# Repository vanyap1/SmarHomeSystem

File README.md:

# SmarHomeSystem
My smart home controllers

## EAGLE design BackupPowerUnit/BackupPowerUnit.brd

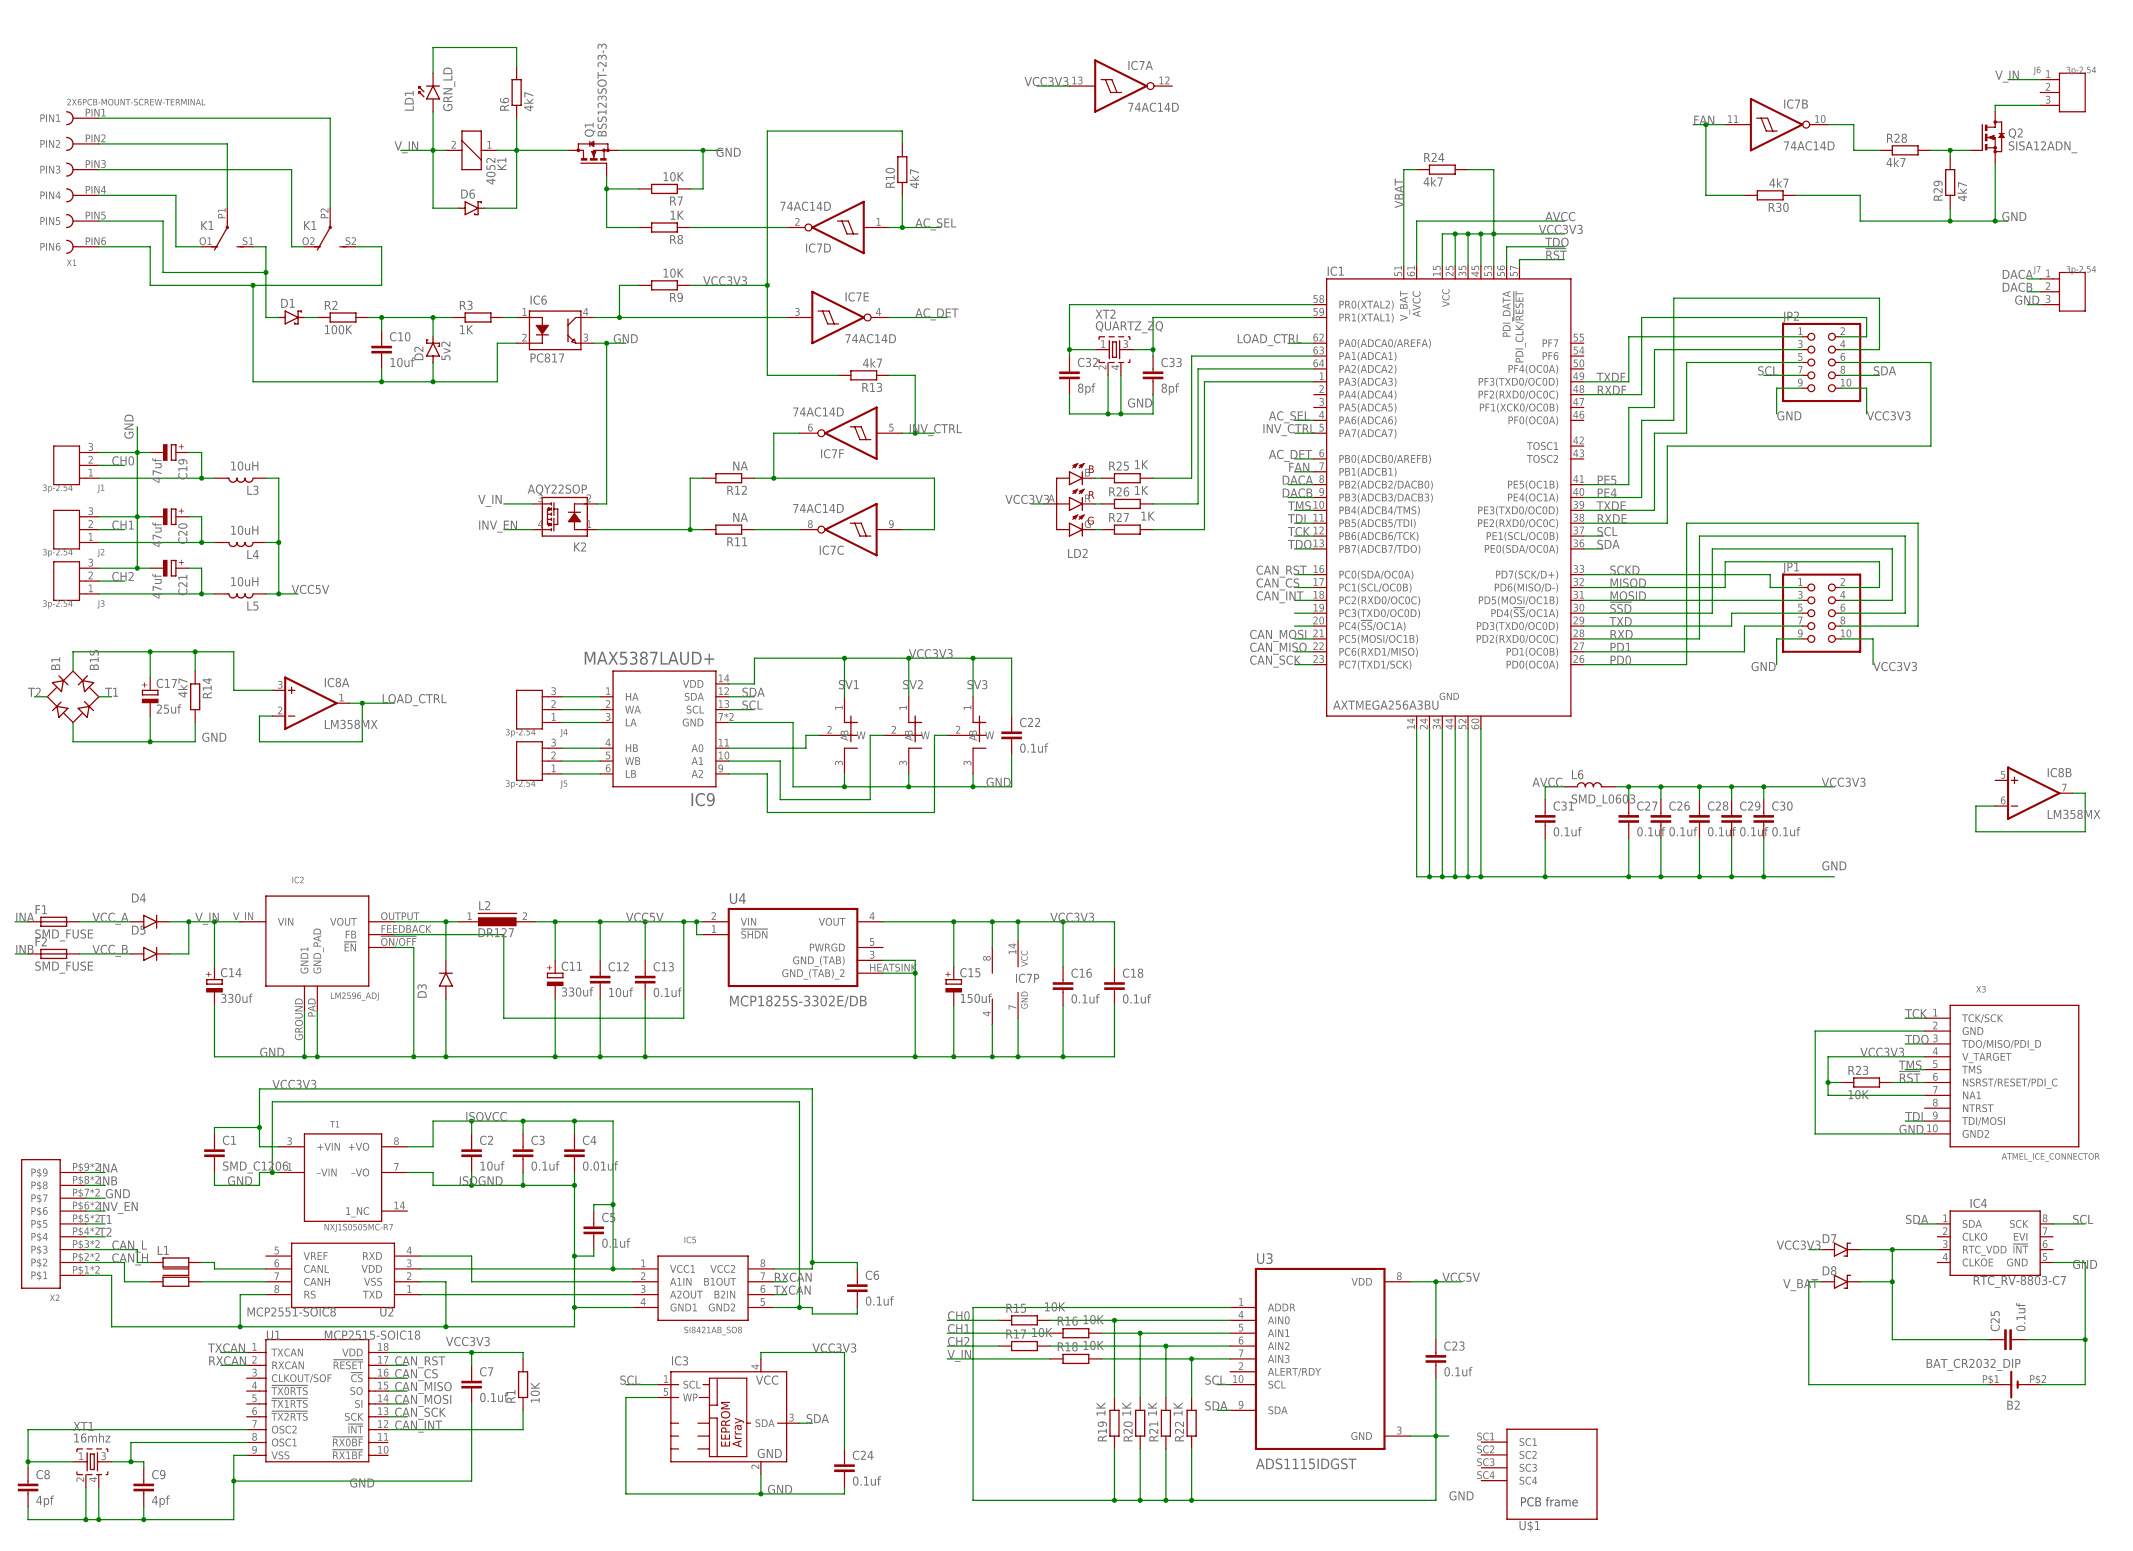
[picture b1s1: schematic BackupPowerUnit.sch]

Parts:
B1: B1S; MBS
B2: BAT_CR2032_DIP; CR2032_DIP
C1: SMD_C1206; 1206
C2, C12: 10uf; 1206
C3, C5, C6, C7, C13, C16, C18, C22, C23, C24, C25, C26, C27, C28, C29, C30, C31: 0.1uf; 0603
C4: 0.01uf; 0603
C8, C9: 4pf; 0603
C10: 10uf; 0805
C11, C14: 330uf; 3.6MM
C15: 150uf; KA-3528ASYC
C17: 25uf; KA-3528ASYC
C19, C20, C21: 47uf; KA-3528ASYC
C32, C33: 8pf; 0603
D1, D6: 1N5819-B; DO41-7.6
D2: 5v2; DO41-7.6
D3, D4, D5: D_MBRA340G; SMA403D
D7, D8: D_SOD323; SOD-323_D
F1, F2: SMD_FUSE; SMD_2410_FUSE_NOK
IC1: AXTMEGA256A3BU; TQFP64
IC2: LM2596_ADJ; DDPAK/TO-263(S)
IC3: MICROCHIP-24AA01T-I/OT; SOT-23(5)
IC4: RTC_RV-8803-C7; C7_RTC
IC5: SI8421AB_SO8; SO8
IC6: PC817; DIL4-SMD
IC7: 74AC14D; SO14
IC8: LM358MX; SO08
IC9: MAX5387LAUD+; SOP65P640X110-14N
J1, J2, J3, J4, J5, J6, J7: 3p-2.54; H3-2.54-7.62X5.8MM
JP1, JP2: PINHD-2X5; 2X05
K1: 4052; F4052
K2: AQY22SOP; SOP04
L1: EPCOS_B82793_FILTER; EPCOS_FILTER
L2: DR127
L3, L4, L5: 10uH; 0603
L6: SMD_L0603; 0603
LD1: GRN_LD; 0603_P
LD2: LTSN-N213EGBW(RGB_LED); LTSN-N213EGBW
Q1: BSS123SOT-23-3; SOT-23(3)
Q2: SISA12ADN_; VISHAY_SIS468DN-T1-GE3
R1, R7, R9, R15, R16, R17, R18, R23: 10K; 0603
R2: 100K; 0204/7
R3, R8, R19, R20, R21, R22, R25, R26, R27: 1K; 0603
R6, R10, R13, R14, R24, R28, R29, R30: 4k7; 0603
R11, R12: NA; 0603
SV1, SV2, SV3: SMD_SWITCH_JUMPER; 0603_JUMP
T1: NXJ1S0505MC-R7; NXJ1SXXXXMC
U1: MCP2515-SOIC18; SO18L
U2: MCP2551-SOIC8; SO8
U3: ADS1115IDGST; SOP50P490X110-10N
U4: MCP1825S-3302E/DB; SOT230P700X180-4N
U$1: JLC_PCB_FRAME80X100_FRAME; 80X100_PCB_FRAME
X1: 2X6PCB-MOUNT-SCREW-TERMINAL
X2: WAGO250_X9; WAGO250_FP_9X
X3: ATMEL_ICE_CONNECTOR; MINI10P_SPI/JTAG/PDI
XT1: 16mhz; QUARTZ_3X3MM
XT2: QUARTZ_ZQ; QUARTZ_3X3MM

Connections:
!RST: IC1.57 (PDI_CLK/!RESET!), R23.2, X3.6 (NSRST/RESET/PDI_C)
!SSD: IC1.30 (PD4(!SS!/OC1A)), JP1.4
AC_DET: IC1.6 (PB0(ADCB0/AREFB)), IC7.4 (O)
AC_SEL: IC1.4 (PA6(ADCA6)), IC7.1 (I), R10.1
AVCC: C31.1, IC1.61 (AVCC), L6.1
CAN_CS: IC1.17 (PC1(SCL/OC0B)), U1.16 (!CS)
CAN_H: L1.P$2 (2), X2.P$2, X2.U$2
CAN_INT: IC1.18 (PC2(RXD0/OC0C)), R1.1, U1.12 (!INT)
CAN_L: L1.P$1 (1), X2.P$3, X2.U$3
CAN_MISO: IC1.22 (PC6(RXD1/MISO)), U1.15 (SO)
CAN_MOSI: IC1.21 (PC5(MOSI/OC1B)), U1.14 (SI)
CAN_RST: IC1.16 (PC0(SDA/OC0A)), U1.17 (!RESET)
CAN_SCK: IC1.23 (PC7(TXD1/SCK)), U1.13 (SCK)
CH0: J1.2, R15.1
CH1: J2.2, R16.1
CH2: J3.2, R17.1
DACA: IC1.8 (PB2(ADCB2/DACB0)), J7.1
DACB: IC1.9 (PB3(ADCB3/DACB3)), J7.2
FAN: IC1.7 (PB1(ADCB1)), IC7.11 (I), R30.2
GND: B1.-, B2.P$2 (-), C1.2, C6.2, C7.2, C8.2, C9.2, C11.P$1 (-), C12.2, C13.2, C14.P$1 (-), C15.M (-), C16.2, C17.M (-), C18.2, C19.M (-), C20.M (-), C21.M (-), C22.2, C23.2, C24.2, C25.2, C26.2, C27.2, C28.2, C29.2, C30.2, C31.2, C32.2, C33.2, D3.P$2 (A), IC1.14 (GND1), IC1.24 (GND2), IC1.34 (GND3), IC1.44 (GND4), IC1.52 (GND5), IC1.60 (GND6), IC2.!ON/OFF (!EN!), IC2.GROUND (GND1), IC2.PAD (GND_PAD), IC3.2 (GND), IC3.5 (WP), IC4.5 (GND), IC5.5 (GND2), IC6.3 (E), IC7.7 (GND), IC8.4 (V-), IC9.7 (GND), IC9.8 (GND), J1.3, J2.3, J3.3, J7.3, JP1.9, JP2.9, K2.2 (K), Q1.2 (S), Q2.1 (S), Q2.2 (S), Q2.3 (S), R7.1, R14.2, R19.1, R20.1, R21.1, R22.1, R29.1, R30.1, SV1.3 (B), SV2.3 (B), SV3.3 (B), T1.1 (–VIN), U1.9 (VSS), U3.1 (ADDR), U3.3 (GND), U4.3 (GND_(TAB)), U4.HEATSINK (GND_(TAB)_2), X2.P$7, X2.U$7, X3.2 (GND), X3.10 (GND2), XT1.2, XT1.4, XT2.2, XT2.4
INA: F1.P$1 (1), X2.P$9, X2.U$9
INB: F2.P$1 (1), X2.P$8, X2.U$8
INV_CTRL: IC1.5 (PA7(ADCA7)), IC7.5 (I), R13.1
INV_EN: K2.4 (DS1), X2.P$6, X2.U$6
ISOGND: C2.2, C3.2, C4.2, C5.2, IC5.4 (GND1), T1.7 (–VO), U2.2 (VSS), U2.8 (RS), X2.P$1, X2.U$1
ISOVCC: C2.1, C3.1, C4.1, C5.1, IC5.1 (VCC1), T1.8 (+VO), U2.3 (VDD)
LOAD_CTRL: IC1.62 (PA0(ADCA0/AREFA)), IC8.1 (OUT), IC8.2 (-IN)
MISOD: IC1.32 (PD6(MISO/D-)), JP1.2
MOSID: IC1.31 (PD5(MOSI/OC1B)), JP1.3
unnamed: D1.A, K1.S1 (S), X1.PIN5
unnamed: K1.O1 (O), X1.PIN4
unnamed: K1.O2 (O), X1.PIN3
unnamed: Q1.1 (G), R7.2, R8.2
unnamed: K1.P1, X1.PIN2
unnamed: K1.P2, X1.PIN1
unnamed: L1.P$3 (3), U2.7 (CANH)
unnamed: L1.P$4 (4), U2.6 (CANL)
unnamed: IC7.6 (O), IC7.9 (I), R12.1
unnamed: IC6.4 (C), IC7.3 (I), R9.2
unnamed: IC5.2 (A1IN), U2.4 (RXD)
unnamed: C9.1, U1.8 (OSC1), XT1.3
unnamed: C8.1, U1.7 (OSC2), XT1.1
unnamed: IC5.3 (A2OUT), U2.1 (TXD)
unnamed: IC6.1 (ANODE), R3.2
unnamed: D3.P$1 (C), IC2.OUTPUT (VOUT), L2.1
unnamed: C10.2, D2.A, IC6.2 (KATODE), K1.S2 (S), X1.PIN6
unnamed: D1.C, R2.1
unnamed: C10.1, D2.C, R2.2, R3.1
unnamed: LD1.1 (K), R6.2
unnamed: D6.C, K1.1, Q1.3 (D), R6.1
unnamed: IC7.2 (O), R8.1
unnamed: K2.1 (A), R11.2, R12.2
unnamed: IC7.8 (O), R11.1
unnamed: IC9.11 (A0), SV1.2 (W)
unnamed: IC8.6 (-IN), IC8.7 (OUT)
unnamed: B1.+, C17.P (+), IC8.3 (+IN), R14.1
unnamed: C19.P (+), J1.1, L3.2
unnamed: IC9.10 (A1), SV2.2 (W)
unnamed: C20.P (+), J2.1, L4.2
unnamed: IC9.9 (A2), SV3.2 (W)
unnamed: C21.P (+), J3.1, L5.2
unnamed: C25.1, D7.K, D8.K, IC4.3 (RTC_VDD)
unnamed: IC9.1 (HA), J4.3
unnamed: IC9.2 (WA), J4.2
unnamed: IC7.10 (O), R28.1
unnamed: IC9.3 (LA), J4.1
unnamed: IC9.4 (HB), J5.3
unnamed: IC9.5 (WB), J5.2
unnamed: IC9.6 (LB), J5.1
unnamed: C33.1, IC1.59 (PR1(XTAL1)), XT2.3
unnamed: R15.2, R19.2, U3.4 (AIN0)
unnamed: R16.2, R20.2, U3.5 (AIN1)
unnamed: R17.2, R21.2, U3.6 (AIN2)
unnamed: R18.2, R22.2, U3.7 (AIN3)
unnamed: C32.1, IC1.58 (PR0(XTAL2)), XT2.1
unnamed: LD2.B (BC), R25.1
unnamed: LD2.R (RC), R26.1
unnamed: LD2.G (GC), R27.1
unnamed: IC1.63 (PA1(ADCA1)), R25.2
unnamed: IC1.64 (PA2(ADCA2)), R26.2
unnamed: IC1.1 (PA3(ADCA3)), R27.2
unnamed: J6.3, Q2.5 (D), Q2.6 (D), Q2.7 (D), Q2.8 (D), Q2.9 (D)
unnamed: Q2.4 (G), R28.2, R29.2
PD0: IC1.26 (PD0(OC0A)), JP1.8
PD1: IC1.27 (PD1(OC0B)), JP1.7
PE4: IC1.40 (PE4(OC1A)), JP2.4
PE5: IC1.41 (PE5(OC1B)), JP2.3
RXCAN: IC5.7 (B1OUT), U1.2 (RXCAN)
RXD: IC1.28 (PD2(RXD0/OC0C)), JP1.6
RXDE: IC1.38 (PE2(RXD0/OC0C)), JP2.6
RXDF: IC1.48 (PF2(RXD0/OC0C)), JP2.2
SCKD: IC1.33 (PD7(SCK/D+)), JP1.1
SCL: IC1.37 (PE1(SCL/OC0B)), IC3.1 (SCL), IC4.8 (SCK), IC9.13 (SCL), JP2.7, U3.10 (SCL)
SDA: IC1.36 (PE0(SDA/OC0A)), IC3.3 (SDA), IC4.1 (SDA), IC9.12 (SDA), JP2.8, U3.9 (SDA)
T1: B1.AC2, X2.P$5, X2.U$5
T2: B1.AC1, X2.P$4, X2.U$4
TCK: IC1.12 (PB6(ADCB6/TCK)), X3.1 (TCK/SCK)
TDI: IC1.11 (PB5(ADCB5/TDI)), X3.9 (TDI/MOSI)
TDO: IC1.13 (PB7(ADCB7/TDO)), IC1.56 (PDI_DATA), X3.3 (TDO/MISO/PDI_D)
TMS: IC1.10 (PB4(ADCB4/TMS)), X3.5 (TMS)
TXCAN: IC5.6 (B2IN), U1.1 (TXCAN)
TXD: IC1.29 (PD3(TXD0/OC0D)), JP1.5
TXDE: IC1.39 (PE3(TXD0/OC0D)), JP2.5
TXDF: IC1.49 (PF3(TXD0/OC0D)), JP2.1
VBAT: IC1.51 (V_BAT), R24.1
VCC3V3: C1.1, C6.1, C7.1, C15.P (+), C16.1, C18.1, C22.1, C24.1, C26.1, C27.1, C28.1, C29.1, C30.1, D7.A, IC1.15 (VCC1), IC1.25 (VCC2), IC1.35 (VCC3), IC1.45 (VCC4), IC1.53 (VCC5), IC3.4 (VCC), IC5.8 (VCC2), IC7.13 (I), IC7.14 (VCC), IC8.8 (V+), IC9.14 (VDD), JP1.10, JP2.10, L6.2, LD2.A, R1.2, R9.1, R10.2, R13.2, R23.1, R24.2, SV1.1 (A), SV2.1 (A), SV3.1 (A), T1.3 (+VIN), U1.18 (VDD), U4.4 (VOUT), X3.4 (V_TARGET), X3.7 (NA1)
VCC5V: C11.P$2 (+), C12.1, C13.1, C23.1, IC2.FEEDBACK (FB), L2.2, L3.1, L4.1, L5.1, U3.8 (VDD), U4.1 (!SHDN), U4.2 (VIN)
VCC_A: D4.P$2 (A), F1.P$2 (2)
VCC_B: D5.P$2 (A), F2.P$2 (2)
V_BAT: B2.P$1 (+), D8.A
V_IN: C14.P$2 (+), D4.P$1 (C), D5.P$1 (C), D6.A, IC2.V_IN (VIN), J6.1, K1.2, K2.3 (DS2), LD1.2 (A), R18.1

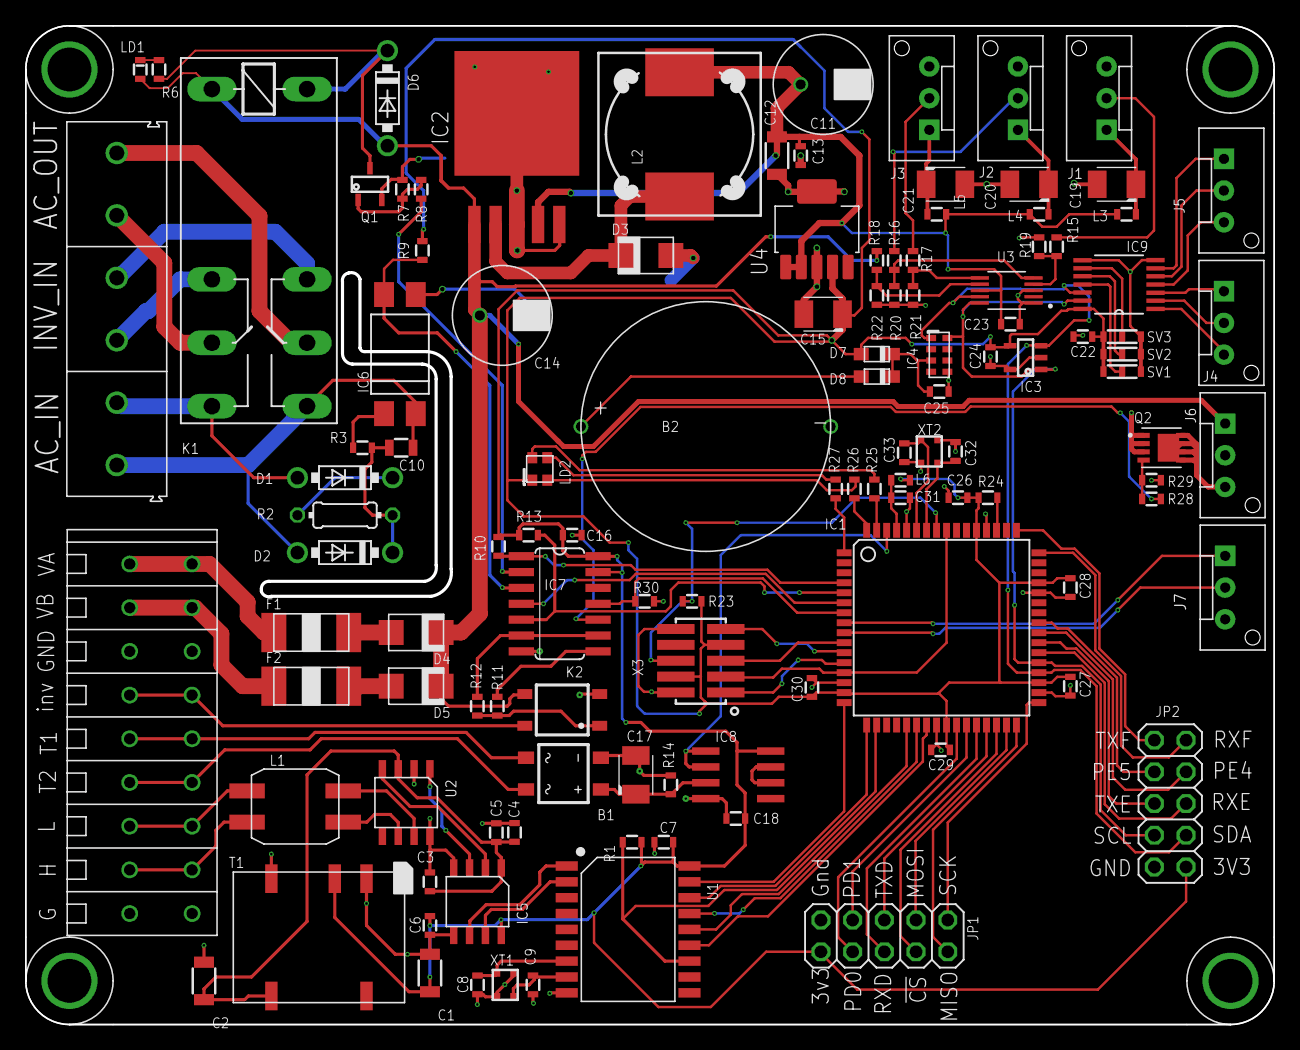
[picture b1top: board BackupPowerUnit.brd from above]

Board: 2 copper layers, 100.0 x 80.0 mm, 117 parts (0 on the bottom side), 111 nets.

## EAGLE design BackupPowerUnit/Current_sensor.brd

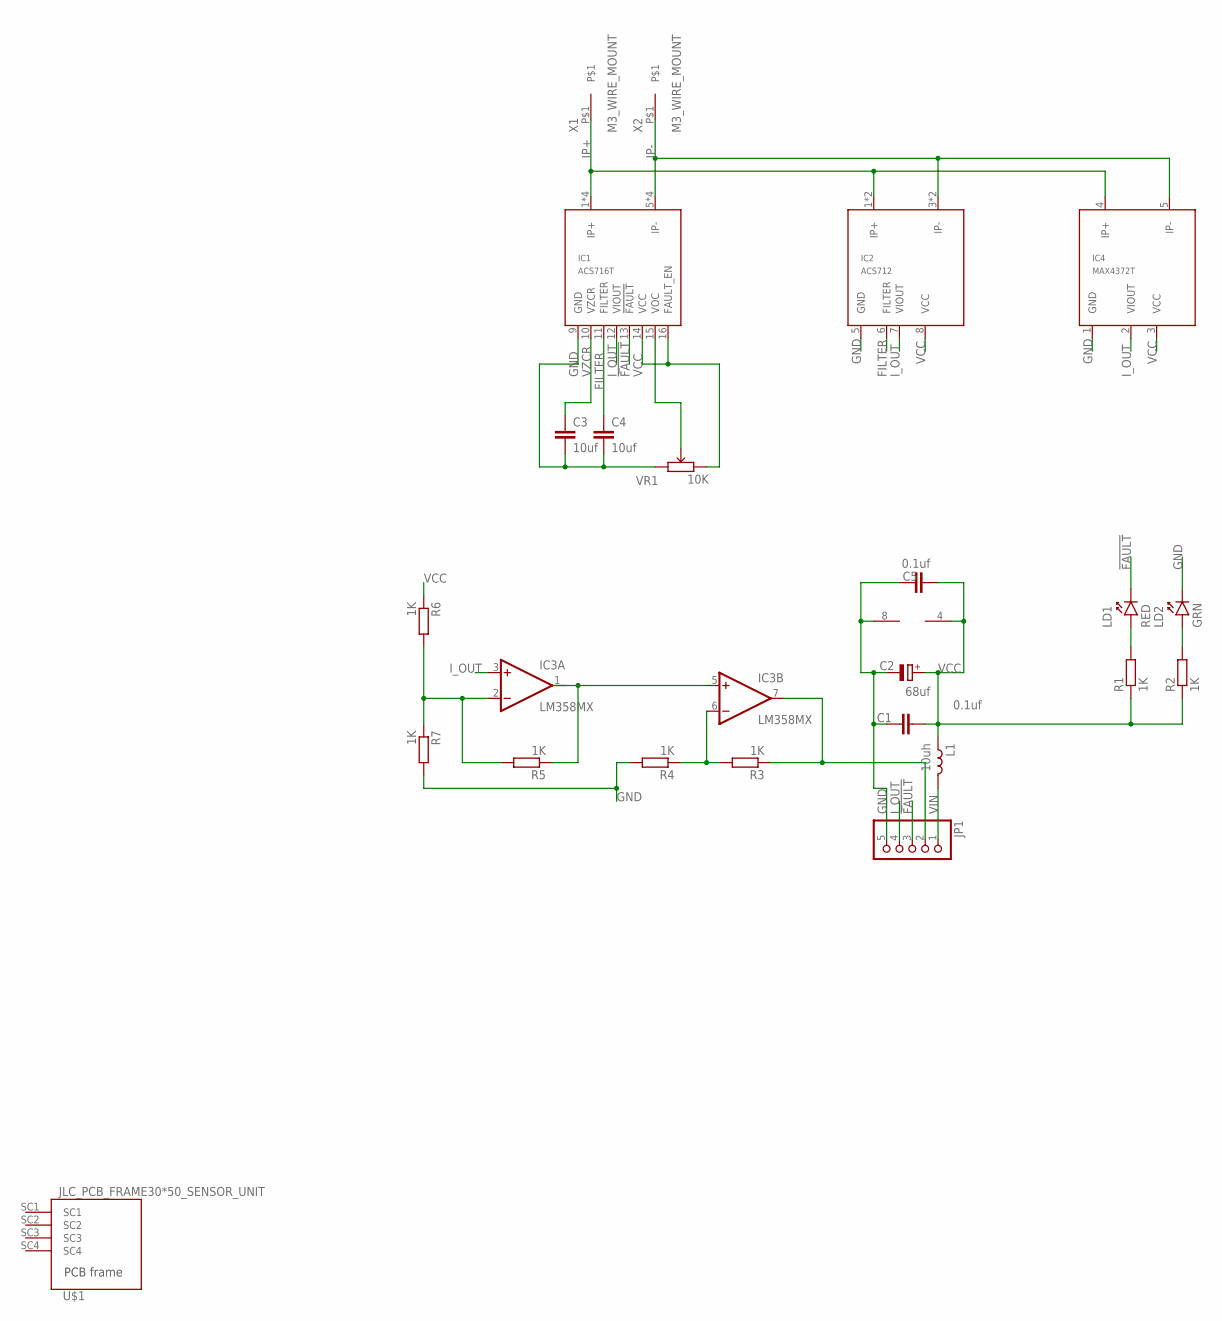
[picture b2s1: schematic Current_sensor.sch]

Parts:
C1, C5: 0.1uf; 0603
C2: 68uf; D/7343-31R
C3, C4: 10uf; 0805
IC1: ACS716T; SO16L
IC2: ACS712; SO8
IC3: LM358MX; SO08
IC4: MAX4372T; SOT-23(5)
JP1: PINHD-1X55X2MM; 1_05X2MM
L1: 10uh; 0603
LD1: RED; 0603_P
LD2: GRN; 0603_P
R1, R2, R3, R4, R5, R6, R7: 1K; 0603
U$1: JLC_PCB_FRAME30*50_SENSOR_UNIT; 30X50_SENSOR_UNIT
VR1: 10K; RESISTOR_VARIABLE
X1, X2: M3_WIRE_MOUNT

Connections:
!FAULT: IC1.13 (!FAULT), JP1.3, LD1.1 (K)
FILTER: C4.1, IC1.11 (FILTER), IC2.6 (FILTER)
GND: C1.1, C2.-, C3.2, C4.2, C5.1, IC1.9 (GND), IC2.5 (GND), IC3.8 (V+), IC4.1 (GND), JP1.5, LD2.1 (K), R4.2, R7.2, VR1.L
IP+: IC1.1 (IP+), IC1.2 (IP+), IC1.3 (IP+), IC1.4 (IP+), IC2.1 (IP+), IC2.2 (IP+), IC4.4 (IP+), X1.P$1
IP-: IC1.5 (IP-), IC1.6 (IP-), IC1.7 (IP-), IC1.8 (IP-), IC2.3 (IP-), IC2.4 (IP-), IC4.5 (IP-), X2.P$1
I_OUT: IC1.12 (VIOUT), IC2.7 (VIOUT), IC3.3 (+IN), IC4.2 (VIOUT), JP1.4
unnamed: IC3.1 (OUT), IC3.5 (+IN), R5.1
unnamed: IC3.6 (-IN), R3.2, R4.1
unnamed: IC3.7 (OUT), JP1.2, R3.1
unnamed: LD1.2 (A), R1.2
unnamed: LD2.2 (A), R2.2
unnamed: IC1.15 (VOC), VR1.W
unnamed: IC3.2 (-IN), R5.2, R6.2, R7.1
VCC: C1.2, C2.+, C5.2, IC1.14 (VCC), IC1.16 (FAULT_EN), IC2.8 (VCC), IC3.4 (V-), IC4.3 (VCC), L1.1, R1.1, R2.1, R6.1, VR1.H
VIN: JP1.1, L1.2
VZCR: C3.1, IC1.10 (VZCR)

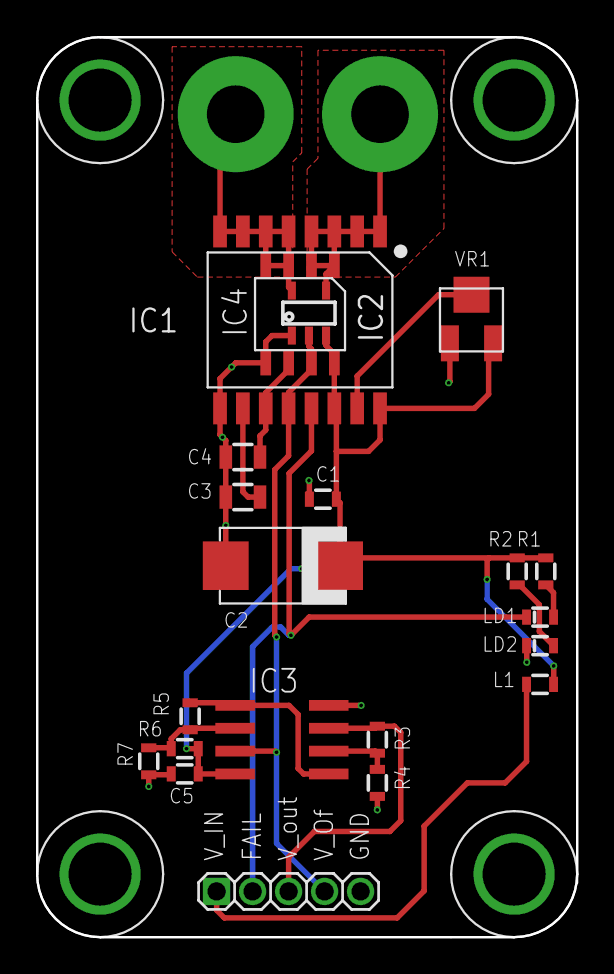
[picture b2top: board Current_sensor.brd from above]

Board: 2 copper layers, 30.0 x 50.0 mm, 24 parts (0 on the bottom side), 16 nets.

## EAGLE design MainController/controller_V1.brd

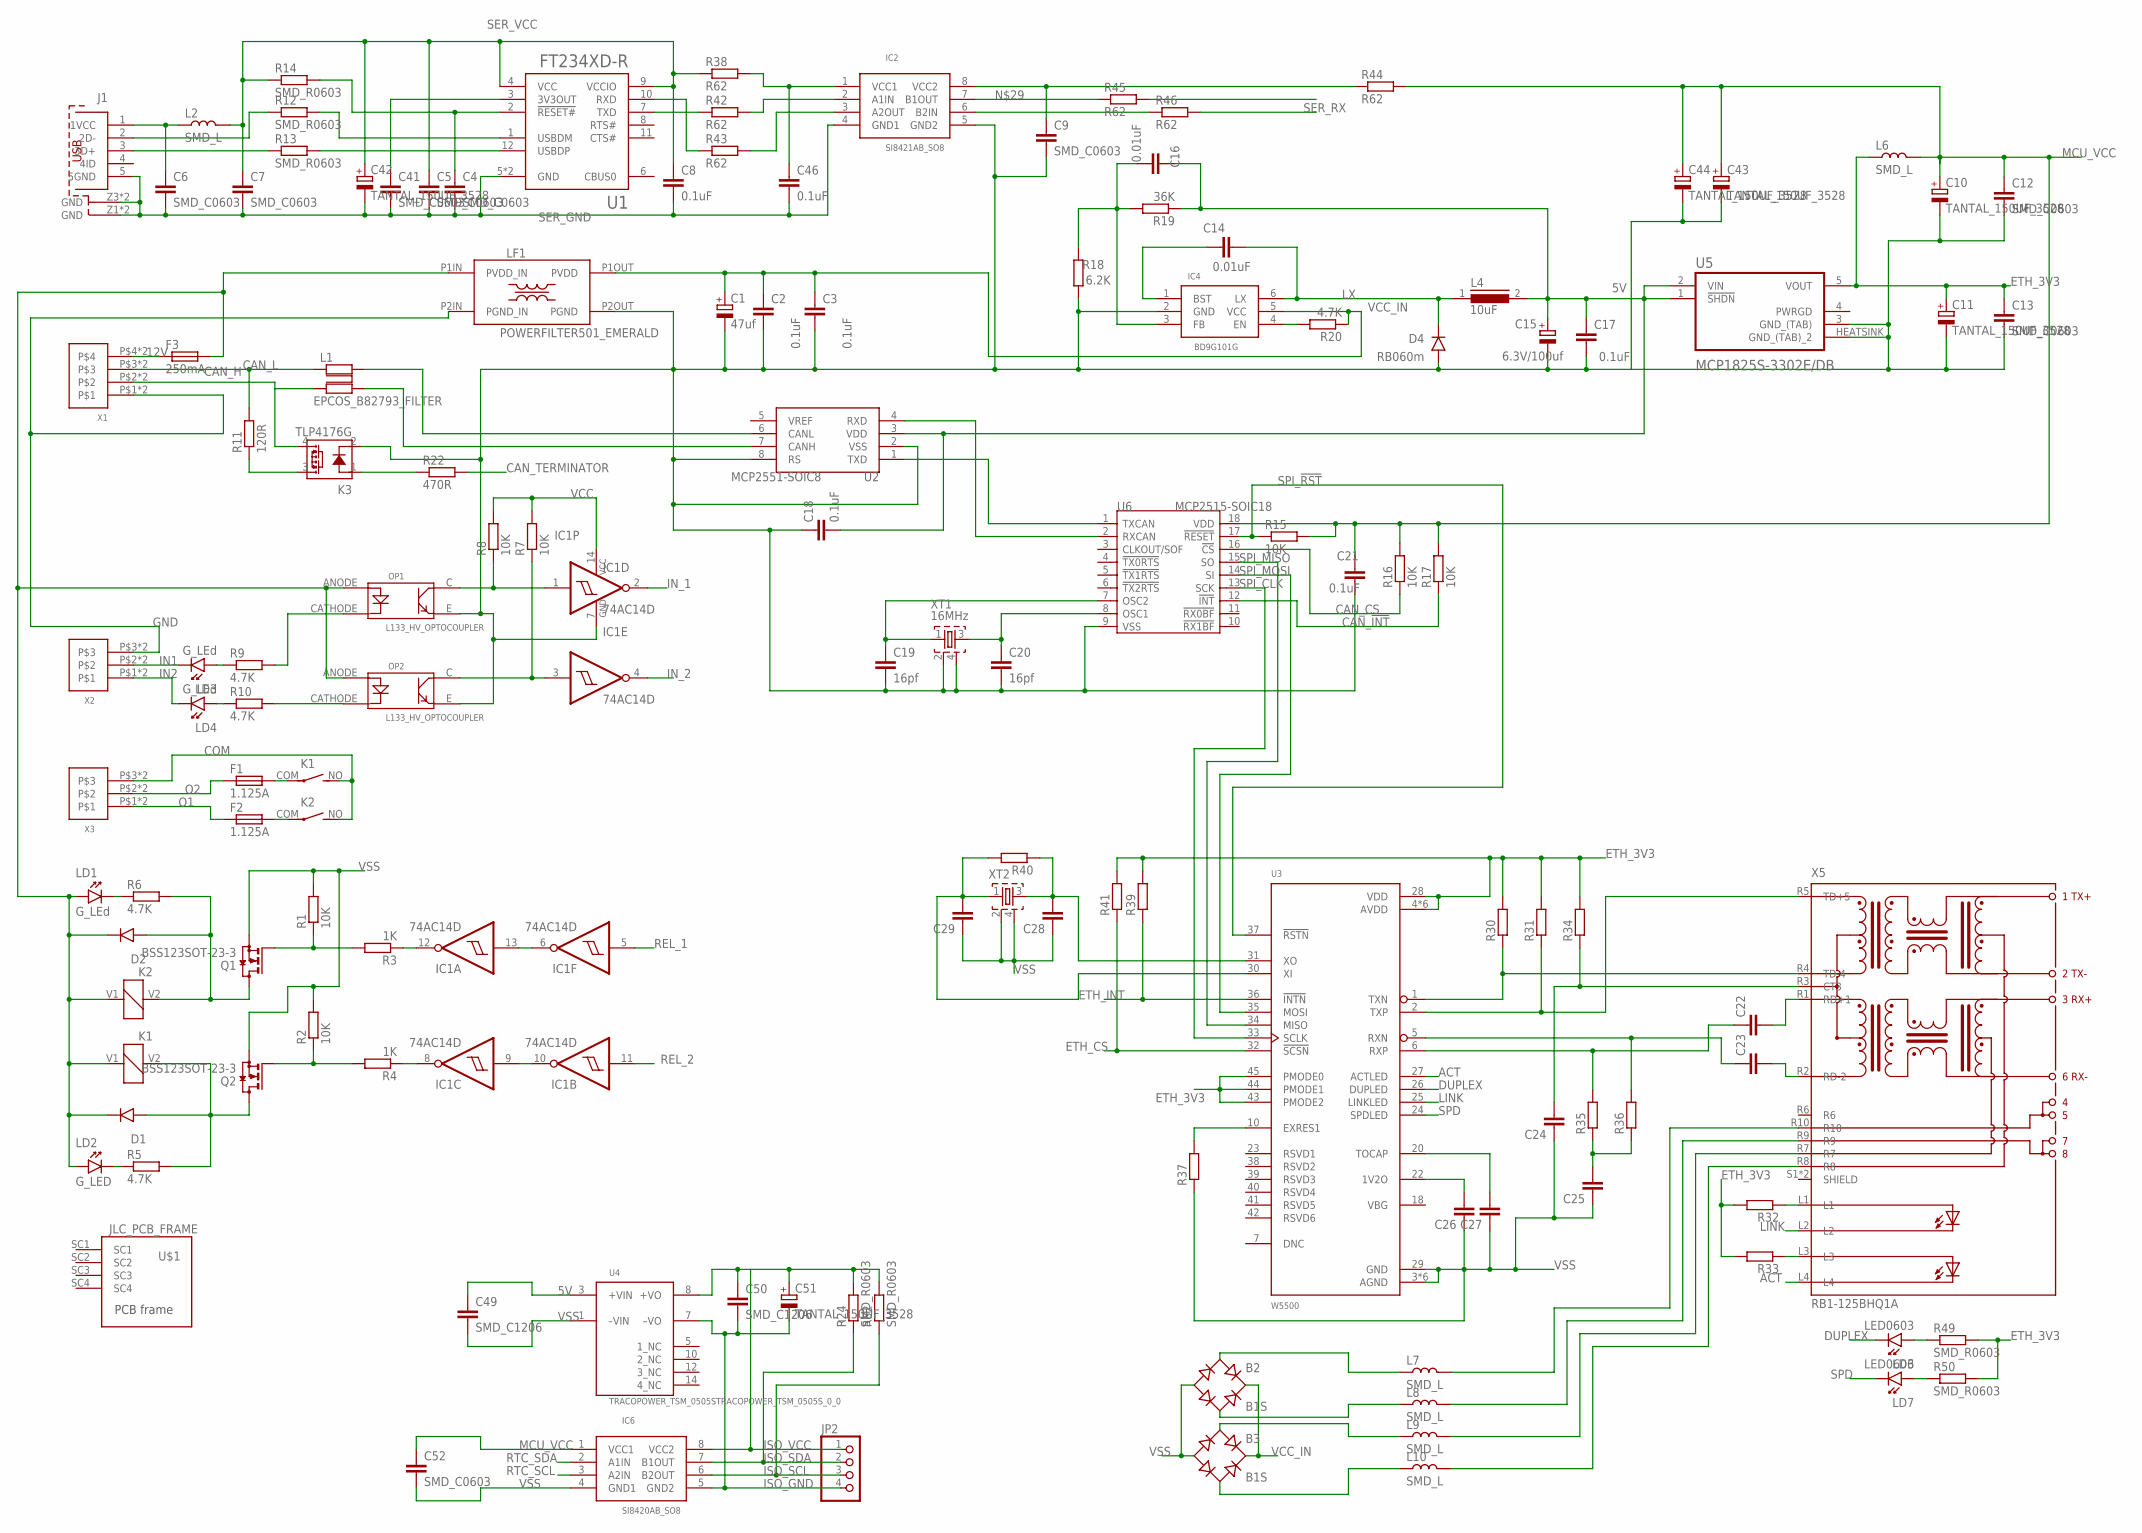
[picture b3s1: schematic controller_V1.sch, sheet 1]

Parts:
B2, B3: B1S; MBS
C1: 47uf; 5.08MM
C2, C3: 0.1uF; 1206
C4, C5, C6, C7, C9, C12, C13, C22, C23, C26, C27, C28, C29, C41, C52: SMD_C0603; 0603
C8, C17, C18, C21, C46: 0.1uF; 0603
C10, C11, C42, C43, C44, C51: TANTAL_150UF_3528; KA-3528ASYC
C14, C16: 0.01uF; 0603
C15: 6.3V/100uf; D/7343-31R
C19, C20: 16pf; 0603
C24: 0.1uf; 0603
C25: 10nf; 0603
C49, C50: SMD_C1206; 1206
D1, D2: D_MBRA340G; SMA403D
D4: RB060m; SMA403D
F1, F2: 1.125A; FUSE_DIP_2.5A250V
F3: 250mA; SMD_2410_FUSE_NOK
IC1: 74AC14D; SO14
IC2: SI8421AB_SO8; SO8
IC4: BD9G101G; SOT-23(6)
IC6: SI8420AB_SO8; SO8
J1: MINI_USB_TYP_B_@; 65100516121
JP2: PINHD-1X4; 1X04
K1, K2: 12-H1(610); 12-H1(610)_DIP
K3: TLP4176G; SOP04
L1: EPCOS_B82793_FILTER; EPCOS_FILTER
L2, L6, L7, L8, L9, L10: SMD_L; 0805
L4: 10uF; DR74
LD1, LD3, LD4: G_LEd; 3MM_DIP_LED
LD2: G_LED; 3MM_DIP_LED
LD6, LD7: LED0603; 0603_P
LF1: POWERFILTER501_EMERALD; POWERFILTER
OP1, OP2: L133_HV_OPTOCOUPLER; HV_OPTOCOUPLER_L133
Q1, Q2: BSS123SOT-23-3; SOT-23(3)
R1, R2, R7, R8, R15, R16, R17: 10K; 0603
R3, R4: 1K; 0603
R5, R6, R9, R10, R20: 4.7K; 0603
R11: 120R; VMTA55
R12, R13, R14, R24, R30, R31, R32, R33, R34, R35, R36, R37, R39, R40, R41, R49, R50, R52: SMD_R0603; 0603
R18: 6.2K; 0603
R19: 36K; 0603
R22: 470R; 0603
R38, R42, R43, R44, R45, R46: R62; 0603
U1: FT234XD-R; IC_FT234XD-R
U2: MCP2551-SOIC8; SO8
U3: W5500; QFP50P900X900X160-48N
U4: TRACOPOWER_TSM_0505STRACOPOWER_TSM_0505S_0_0; TRACOPOWER_TSM_0505S_0
U5: MCP1825S-3302E/DB; SOT230P700X180-4N
U6: MCP2515-SOIC18; SO18L
U$1: JLC_PCB_FRAME; 80X100_PCB_FRAME
X1: WAGO250_X4; WAGO250_FP_4X
X2, X3: WAGO250_X3; WAGO250_FP_3X
X5: RB1-125BHQ1A
XT1: 16MHz; QUARTZ_3X3MM
XT2: QUARTZ_ZQ; QUARTZ_3X3MM

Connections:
5V: C15.+, C16.2, C17.2, C18.2, C49.1, L4.2, R19.1, U2.3 (VDD), U4.3 (+VIN), U5.1 (!SHDN), U5.2 (VIN)
12V: F3.P$1 (1), X1.P$4, X1.U$4
ACT: U3.27 (ACTLED), X5.L4
CAN_!INT: R17.1, U6.12 (!INT); also elsewhere on the board
CAN_CS: R16.1, U6.16 (!CS); also elsewhere on the board
CAN_H: K3.4 (DS2), L1.P$2 (2), X1.P$2, X1.U$2
CAN_L: L1.P$1 (1), R11.2, X1.P$3, X1.U$3
CAN_TERMINATOR: R22.2; also elsewhere on the board
COM: K1.NO (S), K2.NO (S), X3.P$3, X3.U$3
DUPLEX: LD6.1 (K), U3.26 (DUPLED)
ETH_3V3: C11.P (+), C13.1, L6.1, R30.2, R31.2, R32.2, R33.2, R34.2, R39.2, R41.2, R49.2, R50.2, U3.4 (AVDD), U3.8 (AVDD), U3.11 (AVDD), U3.15 (AVDD), U3.17 (AVDD), U3.21 (AVDD), U3.28 (VDD), U3.43 (PMODE2), U3.44 (PMODE1), U3.45 (PMODE0), U5.5 (VOUT)
ETH_CS: R41.1, U3.32 (!SCSN); also elsewhere on the board
ETH_INT: R39.1, U3.36 (!INTN); also elsewhere on the board
GND: LF1.P2IN (PGND_IN), X1.P$1, X1.U$1, X2.P$3, X2.U$3
IN1: LD3.K, X2.P$2, X2.U$2
IN2: LD4.K, X2.P$1, X2.U$1
IN_1: IC1.2 (O); also elsewhere on the board
IN_2: IC1.4 (O); also elsewhere on the board
ISO_GND: C50.2, C51.M (-), IC6.5 (GND2), JP2.4, U4.7 (–VO)
ISO_SCL: IC6.6 (B2OUT), JP2.3, R52.1
ISO_SDA: IC6.7 (B1OUT), JP2.2, R24.1
ISO_VCC: C50.1, C51.P (+), IC6.8 (VCC2), JP2.1, R24.2, R52.2, U4.8 (+VO)
LINK: U3.25 (LINKLED), X5.L2
LX: C14.2, D4.P$1 (C), IC4.6 (LX), L4.1
MCU_VCC: C10.P (+), C12.1, C21.1, C43.P (+), C44.P (+), C52.1, IC6.1 (VCC1), L6.2, R15.2, R16.2, R17.2, R44.2, U6.18 (VDD); also elsewhere on the board
unnamed: IC2.3 (A2OUT), R43.2
unnamed: F1.P$2 (2), K1.COM
unnamed: F2.P$2 (2), K2.COM
unnamed: C41.1, U1.3 (3V3OUT)
unnamed: Q2.1 (G), R2.1, R4.2
unnamed: D1.P$2 (A), K1.V2 (2), Q2.3 (D), R5.2
unnamed: D2.P$2 (A), K2.V2 (2), Q1.3 (D), R6.2
unnamed: Q1.1 (G), R1.1, R3.2
unnamed: LD1.K, R6.1
unnamed: LD2.K, R5.1
unnamed: IC2.2 (A1IN), R42.2
unnamed: IC1.9 (I), IC1.10 (O)
unnamed: IC1.8 (O), R4.1
unnamed: IC1.6 (O), IC1.13 (I)
unnamed: IC1.12 (O), R3.1
unnamed: IC1.1 (I), OP1.C (COLLECTOR), R8.1
unnamed: IC1.3 (I), OP2.C (COLLECTOR), R7.1
unnamed: L10.2, X5.R8
unnamed: C46.1, IC2.1 (VCC1), R38.2
unnamed: D1.P$1 (C), D2.P$1 (C), F3.P$2 (2), K1.V1 (1), K2.V1 (1), LD1.A, LD2.A, LF1.P1IN (PVDD_IN), OP1.ANODE (ANOD), OP2.ANODE (ANOD)
unnamed: OP2.CATHODE (CATHOD), R10.2
unnamed: OP1.CATHODE (CATHOD), R9.2
unnamed: LD3.A, R9.1
unnamed: LD4.A, R10.1
unnamed: C9.1, IC2.8 (VCC2), R44.1
unnamed: IC2.7 (B1OUT), R45.1
unnamed: IC2.6 (B2IN), R46.1
unnamed: K3.3 (DS1), R11.1
unnamed: U2.1 (TXD), U6.1 (TXCAN)
unnamed: J1.3 (3D+), R13.1
unnamed: U2.4 (RXD), U6.2 (RXCAN)
unnamed: R13.2, U1.12 (USBDP)
unnamed: R12.2, U1.1 (USBDM)
unnamed: J1.2 (2D-), R12.1
unnamed: C4.1, R14.2, U1.2 (!RESET#)
unnamed: R42.1, U1.7 (TXD)
unnamed: C6.1, J1.1 (1VCC), L2.1
unnamed: L9.2, X5.R7
unnamed: L8.2, X5.R9
unnamed: R43.1, U1.10 (RXD)
unnamed: L1.P$3 (3), U2.7 (CANH)
unnamed: L1.P$4 (4), U2.6 (CANL)
unnamed: C14.1, IC4.1 (BST)
unnamed: L7.2, X5.R10
unnamed: C16.1, IC4.3 (FB), R18.2, R19.2
unnamed: IC4.4 (EN), R20.2
unnamed: C19.1, U6.7 (OSC2), XT1.1
unnamed: K3.1 (A), R22.1
unnamed: C20.1, U6.8 (OSC1), XT1.3
unnamed: B2.AC1, L7.1
unnamed: B2.AC2, L8.1
unnamed: B3.AC1, L9.1
unnamed: B3.AC2, L10.1
unnamed: LD6.2 (A), R49.1
unnamed: LD7.2 (A), R50.1
unnamed: C22.1, R35.2, U3.6 (RXP)
unnamed: C23.1, R36.2, U3.5 (RXN)
unnamed: R30.1, U3.1 (TXN), X5.R4 (TD-4)
unnamed: R31.1, U3.2 (TXP), X5.R5 (TD+5)
unnamed: C24.2, R34.1, X5.R3 (CT3)
unnamed: C25.2, R35.1, R36.1
unnamed: C22.2, X5.R1 (RD+1)
unnamed: C23.2, X5.R2 (RD-2)
unnamed: R32.1, X5.L1
unnamed: R33.1, X5.L3
unnamed: C26.2, U3.22 (1V2O)
unnamed: C27.2, U3.20 (TOCAP)
unnamed: R37.2, U3.10 (EXRES1)
unnamed: C29.2, R40.2, U3.30 (XI), XT2.1
unnamed: C28.2, R40.1, U3.31 (XO), XT2.3
O1: F2.P$1 (1), X3.P$1, X3.U$1
O2: F1.P$1 (1), X3.P$2, X3.U$2
REL_1: IC1.5 (I); also elsewhere on the board
REL_2: IC1.11 (I); also elsewhere on the board
RTC_SCL: IC6.3 (A2IN); also elsewhere on the board
RTC_SDA: IC6.2 (A1IN); also elsewhere on the board
SER_GND: C4.2, C5.2, C6.2, C7.2, C8.2, C41.2, C42.M (-), C46.2, IC2.4 (GND1), J1.5 (5GND), J1.Z1 (GND), J1.Z2 (GND), J1.Z3 (GND), J1.Z4 (GND), U1.5 (GND), U1.13 (GND)
SER_RX: R46.2; also elsewhere on the board
SER_TX: R45.2; also elsewhere on the board
SER_VCC: C5.1, C7.1, C8.1, C42.P (+), L2.2, R14.1, R38.1, U1.4 (VCC), U1.9 (VCCIO)
SPD: LD7.1 (K), U3.24 (SPDLED)
SPI_!RST: R15.1, U3.37 (!RSTN), U6.17 (!RESET); also elsewhere on the board
SPI_CLK: U3.33 (SCLK), U6.13 (SCK); also elsewhere on the board
SPI_MISO: U3.34 (MISO), U6.15 (SO); also elsewhere on the board
SPI_MOSI: U3.35 (MOSI), U6.14 (SI); also elsewhere on the board
VCC: IC1.14 (VCC), R7.2, R8.2; also elsewhere on the board
VCC_IN: B2.+, B3.+, C1.P$2 (+), C2.1, C3.1, IC4.5 (VCC), LF1.P1OUT (PVDD), R20.1
VSS: B2.-, B3.-, C1.P$1 (-), C2.2, C3.2, C9.2, C10.M (-), C11.M (-), C12.2, C13.2, C15.-, C17.1, C18.1, C19.2, C20.2, C21.2, C24.1, C25.1, C26.1, C27.1, C28.1, C29.1, C43.M (-), C44.M (-), C49.2, C52.2, D4.P$2 (A), IC1.7 (GND), IC2.5 (GND2), IC4.2 (GND), IC6.4 (GND1), K3.2 (K), LF1.P2OUT (PGND), OP1.E (EMITTER), OP2.E (EMITTER), Q1.2 (S), Q2.2 (S), R1.2, R2.2, R18.1, R37.1, U2.2 (VSS), U2.8 (RS), U3.3 (AGND), U3.9 (AGND), U3.14 (AGND), U3.16 (AGND), U3.19 (AGND), U3.29 (GND), U3.48 (AGND), U4.1 (–VIN), U5.3 (GND_(TAB)), U5.HEATSINK (GND_(TAB)_2), U6.9 (VSS), XT1.2, XT1.4, XT2.2, XT2.4; also elsewhere on the board
